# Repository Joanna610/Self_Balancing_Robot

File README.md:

# Self_Balancing_Robot

The projects include code for Arduino. It collects data from the acceleromiter MPU6050 and modifies them accordingly. The code also turn on and off the motors with PWM. It can do this thanks to H bridge - L293D. The robot try to stabilize itself due to implemented PID algorithm.

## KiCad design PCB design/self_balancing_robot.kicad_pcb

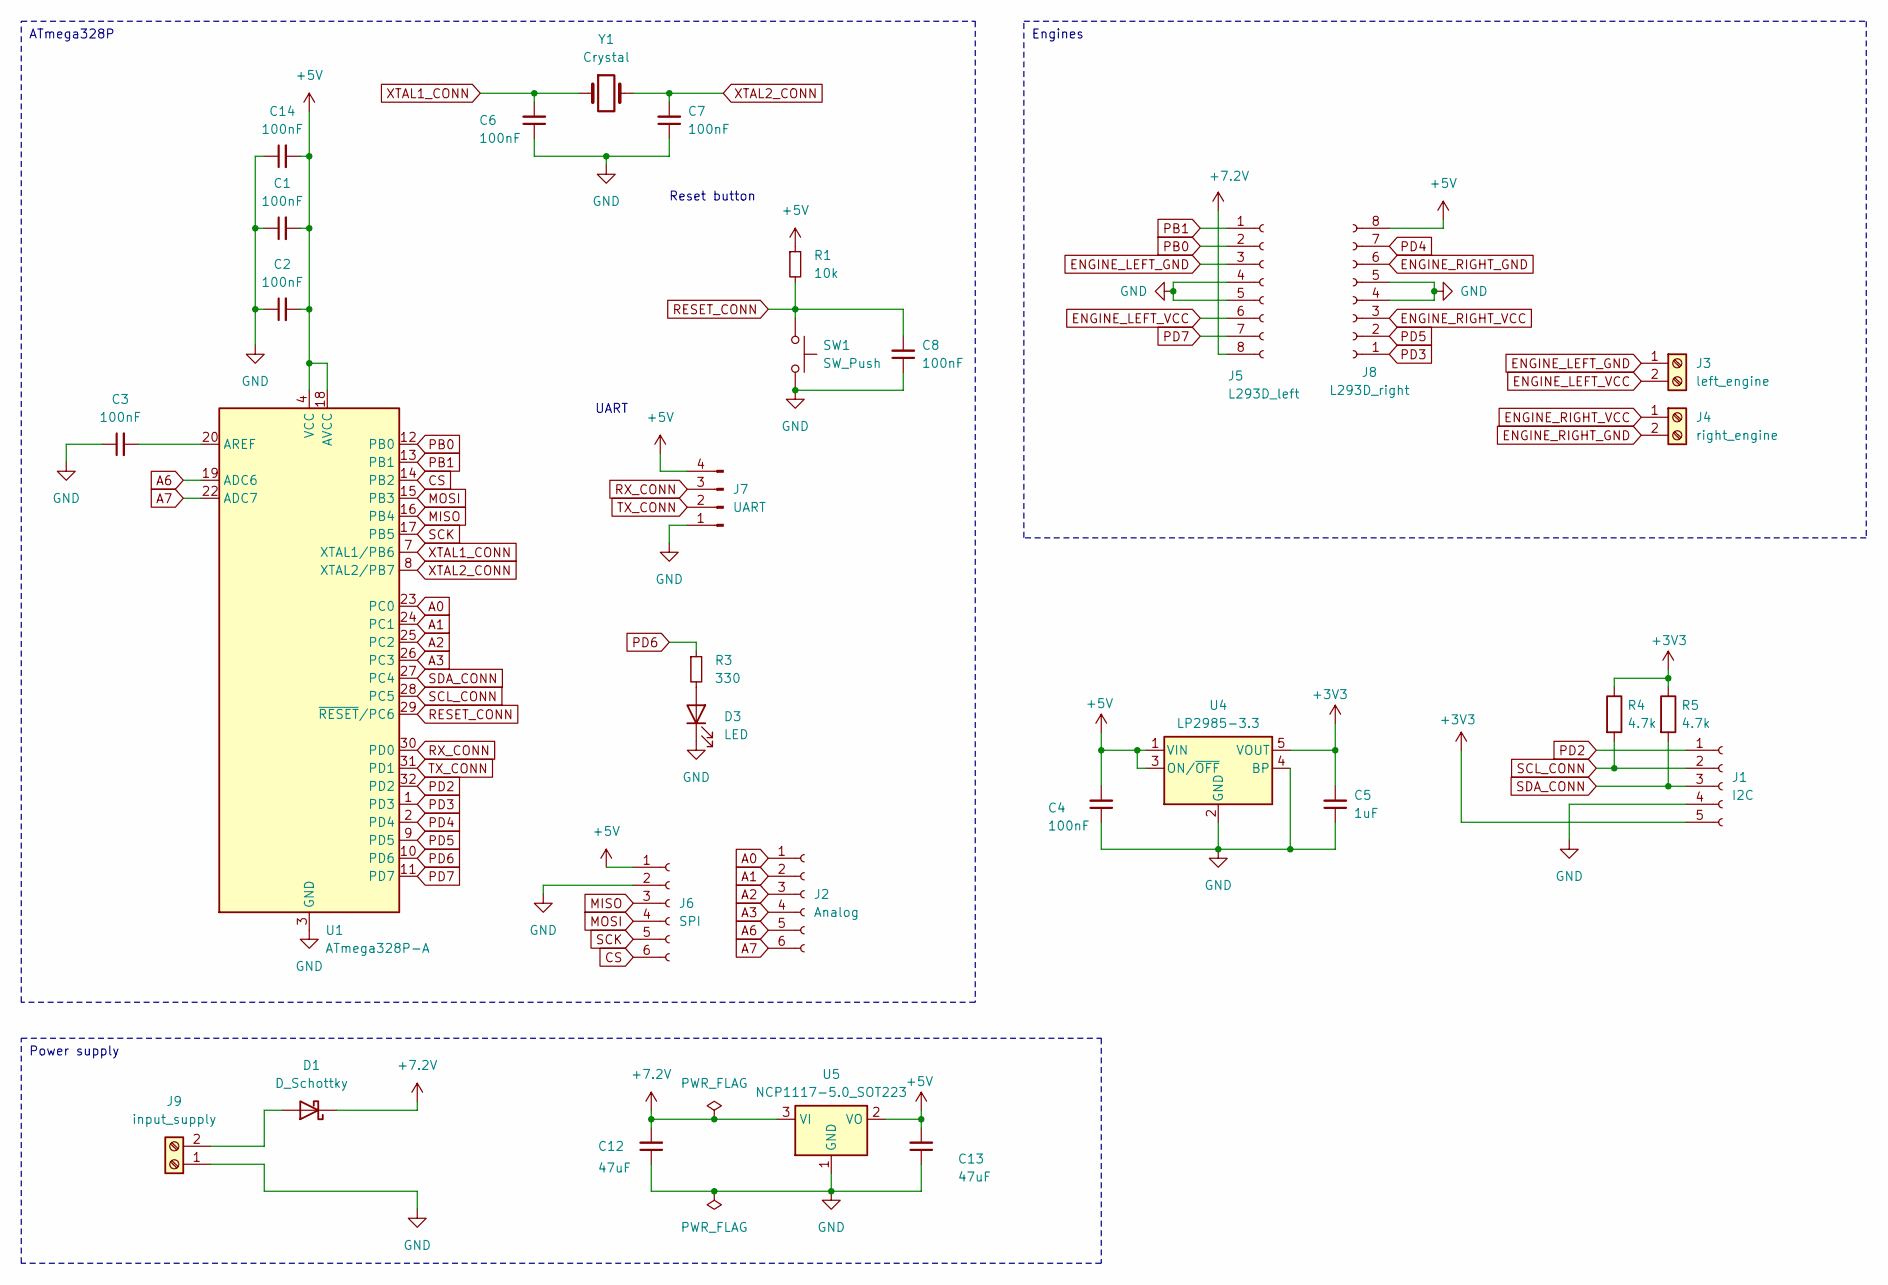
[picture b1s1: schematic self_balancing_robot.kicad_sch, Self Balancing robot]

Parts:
C1, C2, C3, C4, C6, C7, C8, C14: 100nF; C_0805_2012Metric
C5: 1uF; C_0805_2012Metric
C12, C13: 47uF; C_0805_2012Metric
D1: D_Schottky; R_Axial_DIN0207_L6.3mm_D2.5mm_P7.62mm_Horizontal
D3: LED; LED_1206_3216Metric
J1: I2C; PinSocket_1x05_P2.54mm_Vertical
J2: Analog; PinSocket_1x06_P2.54mm_Vertical
J3: left_engine; TE_826576-2_1x02_P3.96mm_Vertical
J4: right_engine; TE_826576-2_1x02_P3.96mm_Vertical
J5: L293D_left; PinSocket_1x08_P2.54mm_Vertical
J6: SPI; PinSocket_1x06_P2.54mm_Vertical
J7: UART; PinHeader_1x04_P2.54mm_Vertical
J8: L293D_right; PinSocket_1x08_P2.54mm_Vertical
J9: input_supply; TE_826576-2_1x02_P3.96mm_Vertical
R1: 10k; R_0805_2012Metric
R3: 330; R_0805_2012Metric
R4, R5: 4.7k; R_0805_2012Metric
SW1: SW_Push; SW_PUSH_1P1T_6x3.5mm_H5.0_APEM_MJTP1250
U1: ATmega328P-A; TQFP-32_7x7mm_P0.8mm
U4: LP2985-3.3; SOT-23-5
U5: NCP1117-5.0_SOT223; SOT-223-3_TabPin2
Y1: Crystal; Crystal_HC49-4H_Vertical

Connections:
+3V3: C5.2, J1.5, R4.1, R5.1, U4.5 (VOUT)
+5V: C1.2, C2.2, C4.2, C13.2, C14.2, J6.1, J7.4, J8.8, R1.1, U1.4 (VCC), U1.6 (VCC), U1.18 (AVCC), U4.1 (VIN), U4.3 (ON/~OFF), U5.2 (VO)
+7.2V: C12.2, D1.1 (K), J5.8, U5.3 (VI)
A0: J2.1, U1.23 (PC0)
A1: J2.2, U1.24 (PC1)
A2: J2.3, U1.25 (PC2)
A3: J2.4, U1.26 (PC3)
A6: J2.5, U1.19 (ADC6)
A7: J2.6, U1.22 (ADC7)
CS: J6.6, U1.14 (PB2)
ENGINE_LEFT_GND: J3.1, J5.3
ENGINE_LEFT_VCC: J3.2, J5.6
ENGINE_RIGHT_GND: J4.2, J8.6
ENGINE_RIGHT_VCC: J4.1, J8.3
GND: C1.1, C2.1, C3.1, C4.1, C5.1, C6.1, C7.1, C8.1, C12.1, C13.1, C14.1, D3.1 (K), J1.4, J5.4, J5.5, J6.2, J7.1, J8.4, J8.5, J9.1, SW1.2, U1.3 (GND), U1.5 (GND), U1.21 (GND), U4.2 (GND), U4.4 (BP), U5.1 (GND)
MISO: J6.3, U1.16 (PB4)
MOSI: J6.4, U1.15 (PB3)
unnamed: D1.2 (A), J9.2
unnamed: D3.2 (A), R3.2
unnamed: C3.2, U1.20 (AREF)
PB0: J5.2, U1.12 (PB0)
PB1: J5.1, U1.13 (PB1)
PD2: J1.1, U1.32 (PD2)
PD3: J8.1, U1.1 (PD3)
PD4: J8.7, U1.2 (PD4)
PD5: J8.2, U1.9 (PD5)
PD6: R3.1, U1.10 (PD6)
PD7: J5.7, U1.11 (PD7)
RESET_CONN: C8.2, R1.2, SW1.1, U1.29 (~RESET/PC6)
RX_CONN: J7.3, U1.30 (PD0)
SCK: J6.5, U1.17 (PB5)
SCL_CONN: J1.2, R4.2, U1.28 (PC5)
SDA_CONN: J1.3, R5.2, U1.27 (PC4)
TX_CONN: J7.2, U1.31 (PD1)
XTAL1_CONN: C6.2, U1.7 (XTAL1/PB6), Y1.1
XTAL2_CONN: C7.2, U1.8 (XTAL2/PB7), Y1.2

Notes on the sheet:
Engines
ATmega328P
Power supply
UART
Reset button

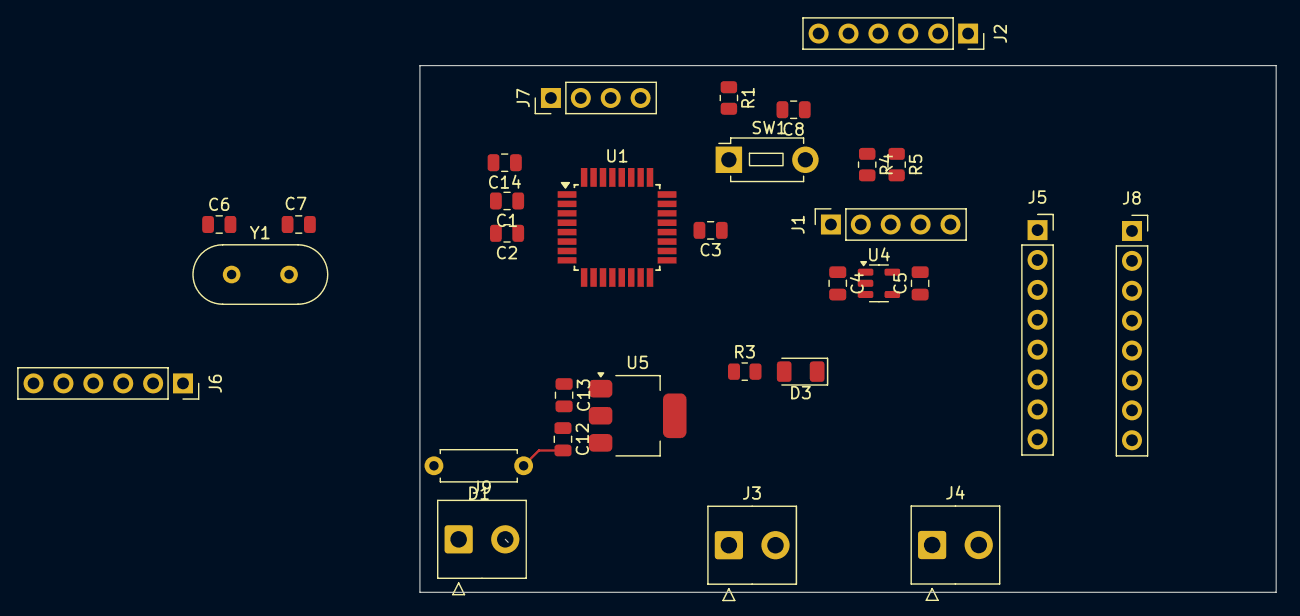
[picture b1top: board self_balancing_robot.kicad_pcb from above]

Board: 2 copper layers, 72.8 x 44.8 mm, 31 parts (0 on the bottom side), 36 nets.

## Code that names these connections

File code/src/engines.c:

#include "engines.h"
#include <stdint.h>
#include <avr/io.h>

// PD6 PB0 PD7
// PB3 PD5 PD4

void initEngines() {
    // Timer1 - Fast PWM, 8-bit, non-inverting, prescaler 64 (dla D9/OC1A)
    TCCR0A |= (1 << COM0A1) | (1 << WGM00) | (1 << WGM01); // Fast PWM na OC0A
    TCCR0B |= (1 << CS01) | (1 << CS00); // prescaler 64

    // Timer2 - Fast PWM, non-inverting, prescaler 64 (dla D3/OC2B)
    TCCR2A |= (1 << COM2B1) | (1 << WGM20) | (1 << WGM21);
    TCCR2B |= (1 << CS22); // prescaler 64

    // Ustaw pozostałe piny jako wyjścia
    DDRB |= (1 << PB0);      // D8 (in1)
    DDRD |= (1 << PD7);      // D7 (in2)
    DDRD |= (1 << PD5);      // D5 (in3)
    DDRD |= (1 << PD4);      // D4 (in4)
    // Set PWM pins as output
    DDRD |= (1 << PD6); // D9 / OC1A
    DDRD |= (1 << PD3); // D3 / OC2B

    // Wyłącz silniki na start
    PORTB &= ~(1 << PB0);    // in1 LOW
    PORTD &= ~(1 << PD7);    // in2 LOW
    PORTD &= ~(1 << PD5);    // in3 LOW
    PORTD &= ~(1 << PD4);    // in4 LOW
}

void forward(int speed) {
    OCR0A = speed; // PWM na D9 (enA)
    OCR2B = speed; // PWM na D3 (enB)

    // Motor A forward
    PORTB |= (1 << PB0);  // in1 HIGH
    PORTD &= ~(1 << PD7); // in2 LOW

    // Motor B forward
    PORTD |= (1 << PD5);  // in3 HIGH
    PORTD &= ~(1 << PD4); // in4 LOW
}

void backward(int speed) {
    OCR0A = speed; // PWM na D9 (enA)
    OCR2B = speed; // PWM na D3 (enB)

    // Motor A forward
    PORTB &= ~(1 << PB0);  // in1 HIGH
    PORTD |= (1 << PD7); // in2 LOW

    // Motor B forward
    PORTD &= ~(1 << PD5);  // in3 HIGH
    PORTD |= (1 << PD4); // in4 LOW
}

void stop() {
    PORTB &= ~(1 << PB0);    // in1 LOW
    PORTD &= ~(1 << PD7);    // in2 LOW
    PORTD &= ~(1 << PD5);    // in3 LOW
    PORTD &= ~(1 << PD4);    // in4 LOW
}

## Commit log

2025-04-09 Adding code
2025-04-10 Code changing
2025-05-14 First PCB model attempt
2025-05-16 PCB update
2025-05-28 PCB update - almost finishing
2025-05-31 code update
2025-05-31 code update - PID tunning
2025-06-30 The first stage of construction
2025-07-01 test branch
